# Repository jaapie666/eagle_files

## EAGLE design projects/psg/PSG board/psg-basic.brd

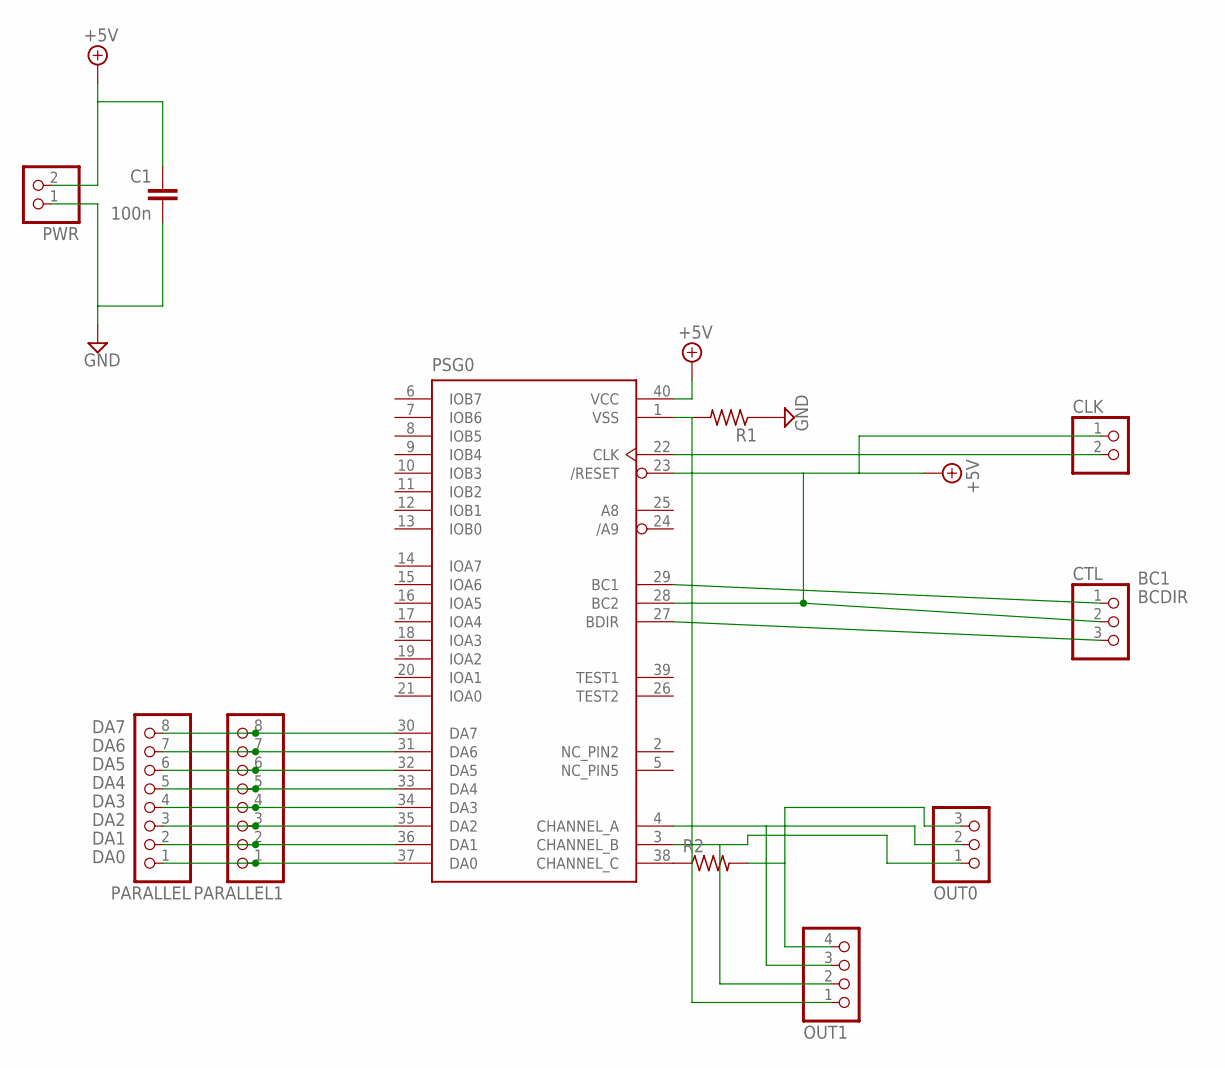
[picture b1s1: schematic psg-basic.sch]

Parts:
C1: 100n; 050X030_025
CLK: PINHD-1X2; 1X02
CTL: PINHD-1X3; 1X03
OUT0: PINHD-1X3; 1X03
OUT1: PINHD-1X4/90; 1X04/90
PARALLEL, PARALLEL1: PINHD-1X8; 1X08
PSG0: AY-3-8910; DIL40
PWR: PINHD-1X2; 1X02
R1: 6MM.4.1; R0207/4A
R2: 6MM.5; R0207/5

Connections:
+5V: C1.1, CLK.1, CTL.2, PSG0.23 (/RESET), PSG0.28 (BC2), PSG0.40 (VCC), PWR.2
BC1: CTL.1, PSG0.29 (BC1)
BCDIR: CTL.3, PSG0.27 (BDIR)
DA0: PARALLEL.1, PARALLEL1.1, PSG0.37 (DA0)
DA1: PARALLEL.2, PARALLEL1.2, PSG0.36 (DA1)
DA2: PARALLEL.3, PARALLEL1.3, PSG0.35 (DA2)
DA3: PARALLEL.4, PARALLEL1.4, PSG0.34 (DA3)
DA4: PARALLEL.5, PARALLEL1.5, PSG0.33 (DA4)
DA5: PARALLEL.6, PARALLEL1.6, PSG0.32 (DA5)
DA6: PARALLEL.7, PARALLEL1.7, PSG0.31 (DA6)
DA7: PARALLEL.8, PARALLEL1.8, PSG0.30 (DA7)
GND: C1.2, PWR.1, R1.1
unnamed: PSG0.38 (CHANNEL_C), R2.1
unnamed: OUT0.3, OUT1.4, R2.2
unnamed: CLK.2, PSG0.22 (CLK)
unnamed: OUT0.2, OUT1.3, PSG0.4 (CHANNEL_A)
unnamed: OUT0.1, OUT1.2, PSG0.3 (CHANNEL_B)
unnamed: OUT1.1, PSG0.1 (VSS), R1.2

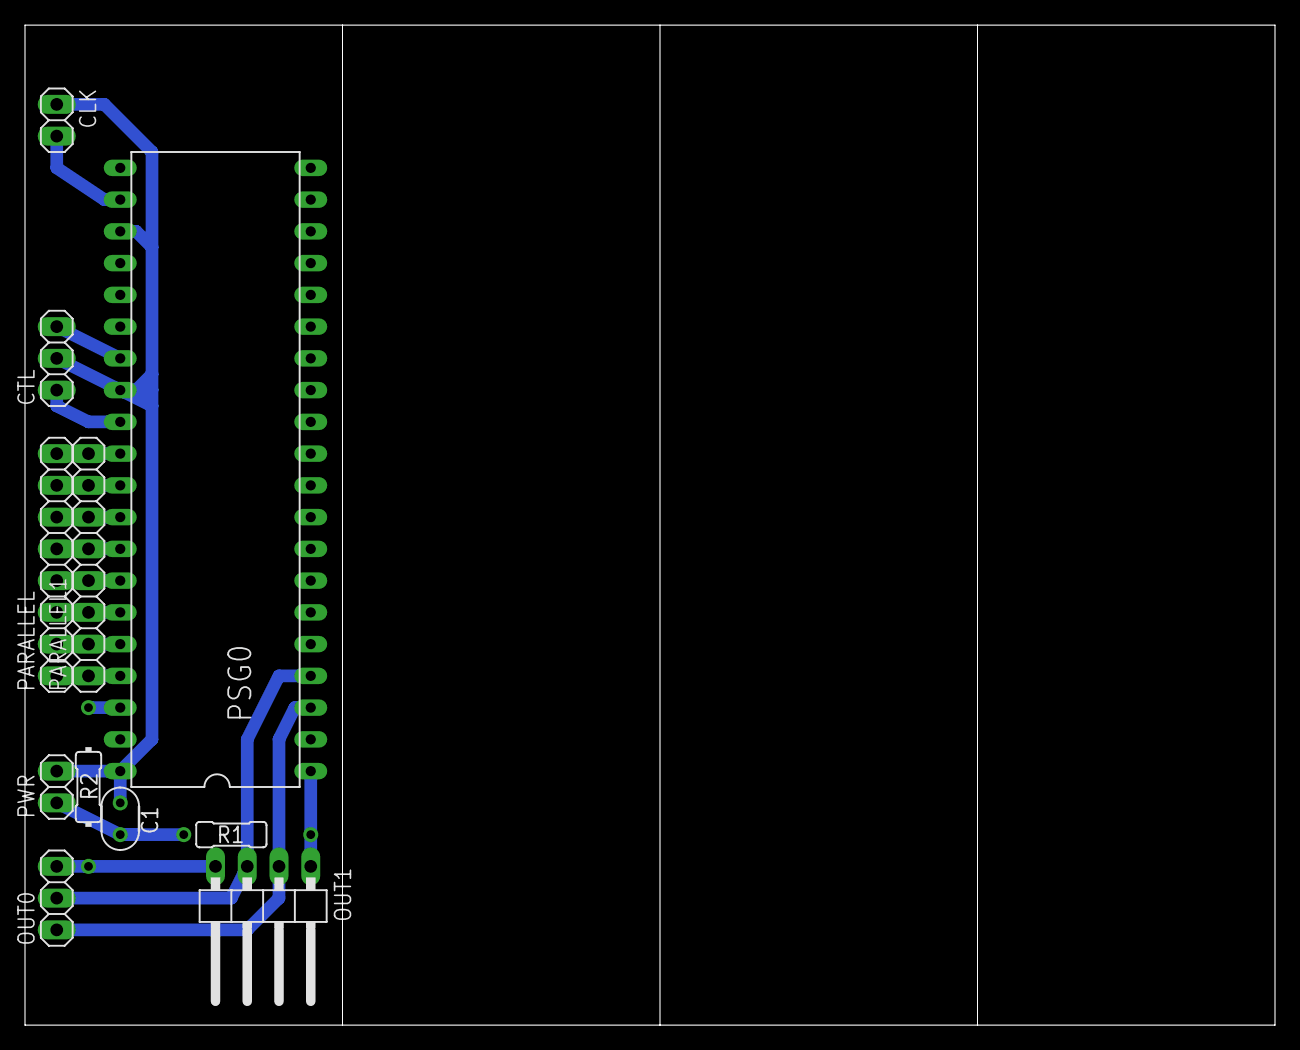
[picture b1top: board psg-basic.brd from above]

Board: 2 copper layers, 100.0 x 80.0 mm, 11 parts (0 on the bottom side), 18 nets.

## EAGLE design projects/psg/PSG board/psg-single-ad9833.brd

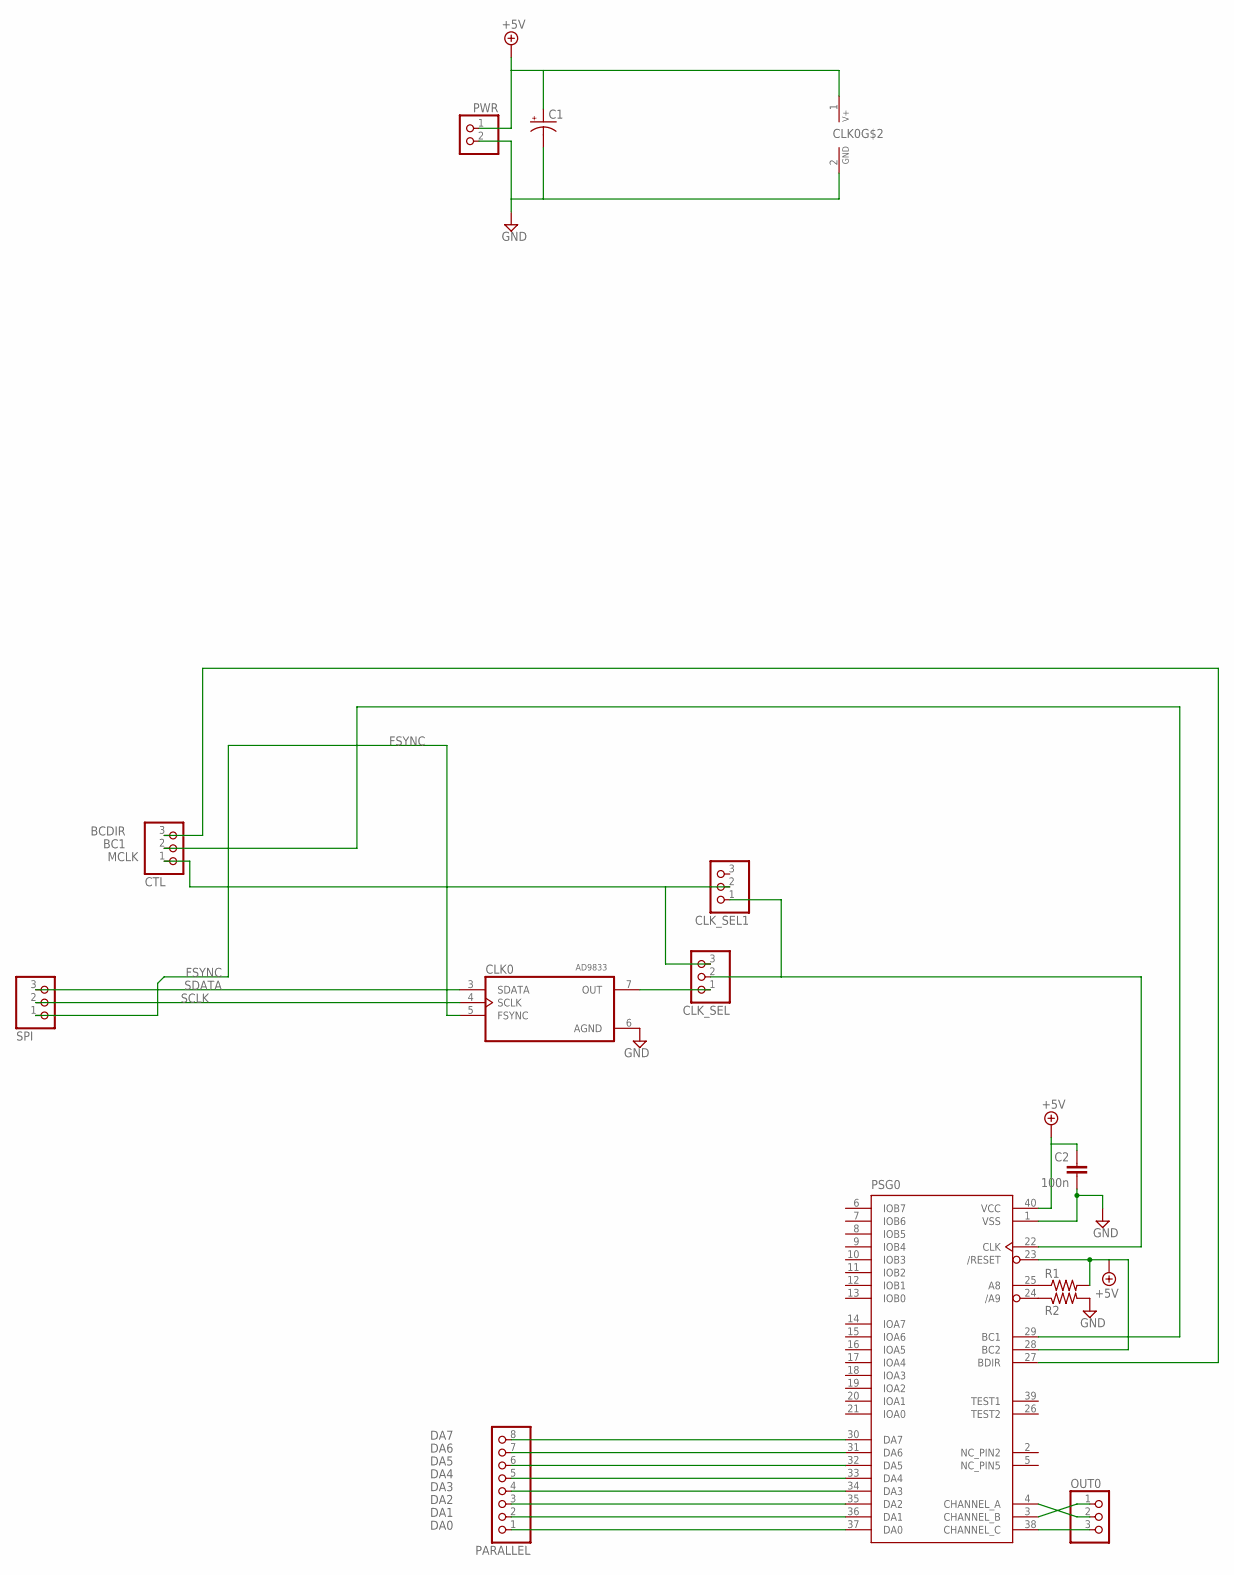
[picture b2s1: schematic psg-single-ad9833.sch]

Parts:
C1: 0501; 050_020_1
C2: 100n; 050X030_025
CLK0: AD9833_MODULE
CLK_SEL, CLK_SEL1: PINHD-1X3/90; 1X03/90
CTL: PINHD-1X3/90; 1X03/90
OUT0: PINHD-1X3/90; 1X03/90
PARALLEL: PINHD-1X8/90; 1X08/90
PSG0: AY-3-8910; DIL40
PWR: PINHD-1X2/90; 1X02/90
R1, R2: 6MM.3; R0207/3
SPI: PINHD-1X3/90; 1X03/90

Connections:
+5V: C1.+, C2.1, CLK0.1 (+V), PSG0.23 (/RESET), PSG0.28 (BC2), PSG0.40 (VCC), PWR.1, R1.2
BC1: CTL.2, PSG0.29 (BC1)
BCDIR: CTL.3, PSG0.27 (BDIR)
CLK_IN_0: CLK_SEL.2, CLK_SEL1.1, PSG0.22 (CLK)
DA0: PARALLEL.1, PSG0.37 (DA0)
DA1: PARALLEL.2, PSG0.36 (DA1)
DA2: PARALLEL.3, PSG0.35 (DA2)
DA3: PARALLEL.4, PSG0.34 (DA3)
DA4: PARALLEL.5, PSG0.33 (DA4)
DA5: PARALLEL.6, PSG0.32 (DA5)
DA6: PARALLEL.7, PSG0.31 (DA6)
DA7: PARALLEL.8, PSG0.30 (DA7)
FSYNC: CLK0.5 (FSYNC), SPI.1
GND: C1.-, C2.2, CLK0.2 (GND), CLK0.6 (AGND), PSG0.1 (VSS), PWR.2, R2.2
MCLK: CLK_SEL.3, CLK_SEL1.2, CTL.1
unnamed: CLK0.7 (OUT), CLK_SEL.1
unnamed: PSG0.24 (/A9), R2.1
unnamed: PSG0.25 (A8), R1.1
OUT_A: OUT0.2, PSG0.4 (CHANNEL_A)
OUT_B: OUT0.1, PSG0.3 (CHANNEL_B)
OUT_C: OUT0.3, PSG0.38 (CHANNEL_C)
SCLK: CLK0.4 (SCLK), SPI.2
SDATA: CLK0.3 (SDATA), SPI.3

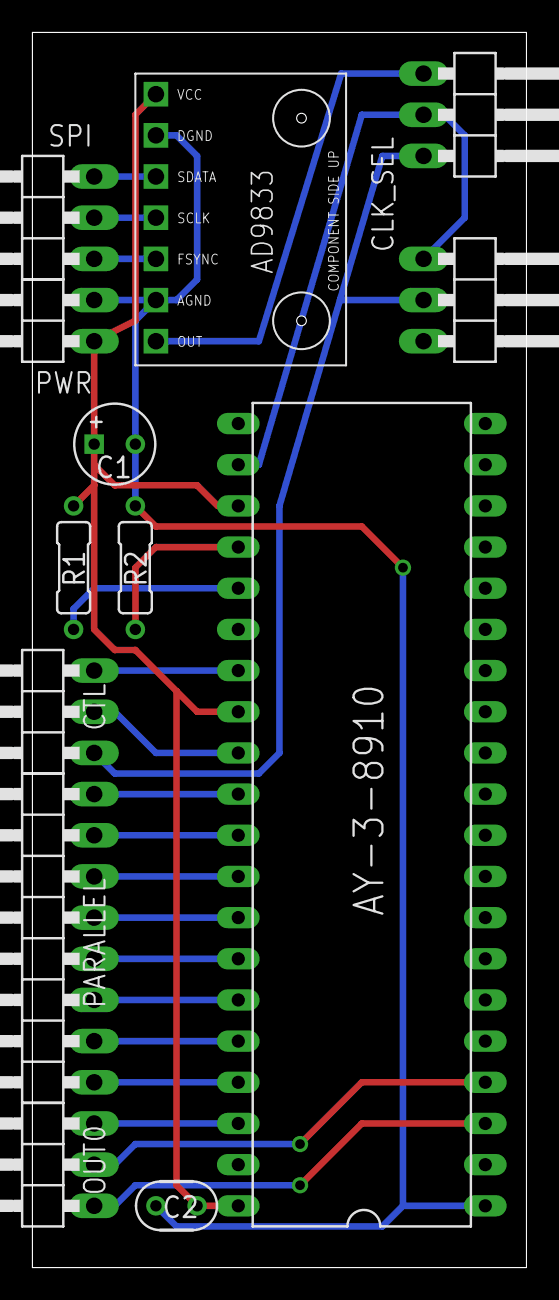
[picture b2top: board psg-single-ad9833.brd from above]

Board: 2 copper layers, 30.5 x 76.2 mm, 13 parts (0 on the bottom side), 23 nets.

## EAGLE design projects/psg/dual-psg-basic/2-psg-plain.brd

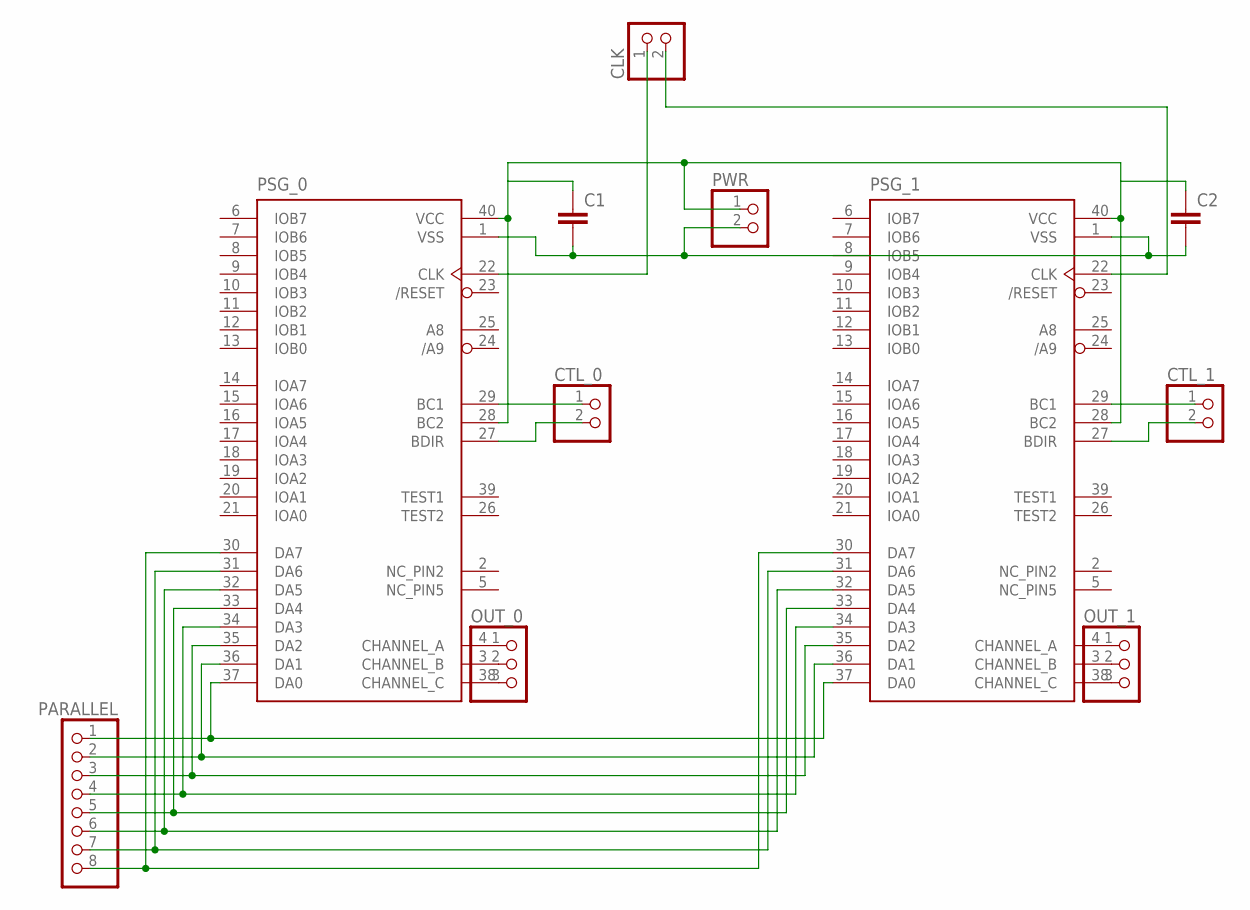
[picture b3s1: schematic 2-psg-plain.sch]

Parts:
C1, C2: 050X030_0251; 050X030_025
CLK: PINHD-1X2; 1X02
CTL_0, CTL_1: PINHD-1X2; 1X02
OUT_0, OUT_1: PINHD-1X3; 1X03
PARALLEL: PINHD-1X8; 1X08
PSG_0, PSG_1: AY-3-8910; DIL40
PWR: PINHD-1X2; 1X02

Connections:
GND: C1.2, C2.2, PSG_0.1 (VSS), PSG_1.1 (VSS), PWR.2
unnamed: CTL_0.2, PSG_0.27 (BDIR)
unnamed: CTL_0.1, PSG_0.29 (BC1)
unnamed: OUT_0.1, PSG_0.4 (CHANNEL_A)
unnamed: OUT_0.2, PSG_0.3 (CHANNEL_B)
unnamed: OUT_0.3, PSG_0.38 (CHANNEL_C)
unnamed: CTL_1.2, PSG_1.27 (BDIR)
unnamed: PARALLEL.1, PSG_0.37 (DA0), PSG_1.37 (DA0)
unnamed: OUT_1.1, PSG_1.4 (CHANNEL_A)
unnamed: PARALLEL.2, PSG_0.36 (DA1), PSG_1.36 (DA1)
unnamed: OUT_1.2, PSG_1.3 (CHANNEL_B)
unnamed: OUT_1.3, PSG_1.38 (CHANNEL_C)
unnamed: CLK.1, PSG_0.22 (CLK)
unnamed: CTL_1.1, PSG_1.29 (BC1)
unnamed: CLK.2, PSG_1.22 (CLK)
unnamed: PARALLEL.3, PSG_0.35 (DA2), PSG_1.35 (DA2)
unnamed: PARALLEL.4, PSG_0.34 (DA3), PSG_1.34 (DA3)
unnamed: PARALLEL.5, PSG_0.33 (DA4), PSG_1.33 (DA4)
unnamed: PARALLEL.6, PSG_0.32 (DA5), PSG_1.32 (DA5)
unnamed: PARALLEL.7, PSG_0.31 (DA6), PSG_1.31 (DA6)
unnamed: PARALLEL.8, PSG_0.30 (DA7), PSG_1.30 (DA7)
VCC: C1.1, C2.1, PSG_0.28 (BC2), PSG_0.40 (VCC), PSG_1.28 (BC2), PSG_1.40 (VCC), PWR.1

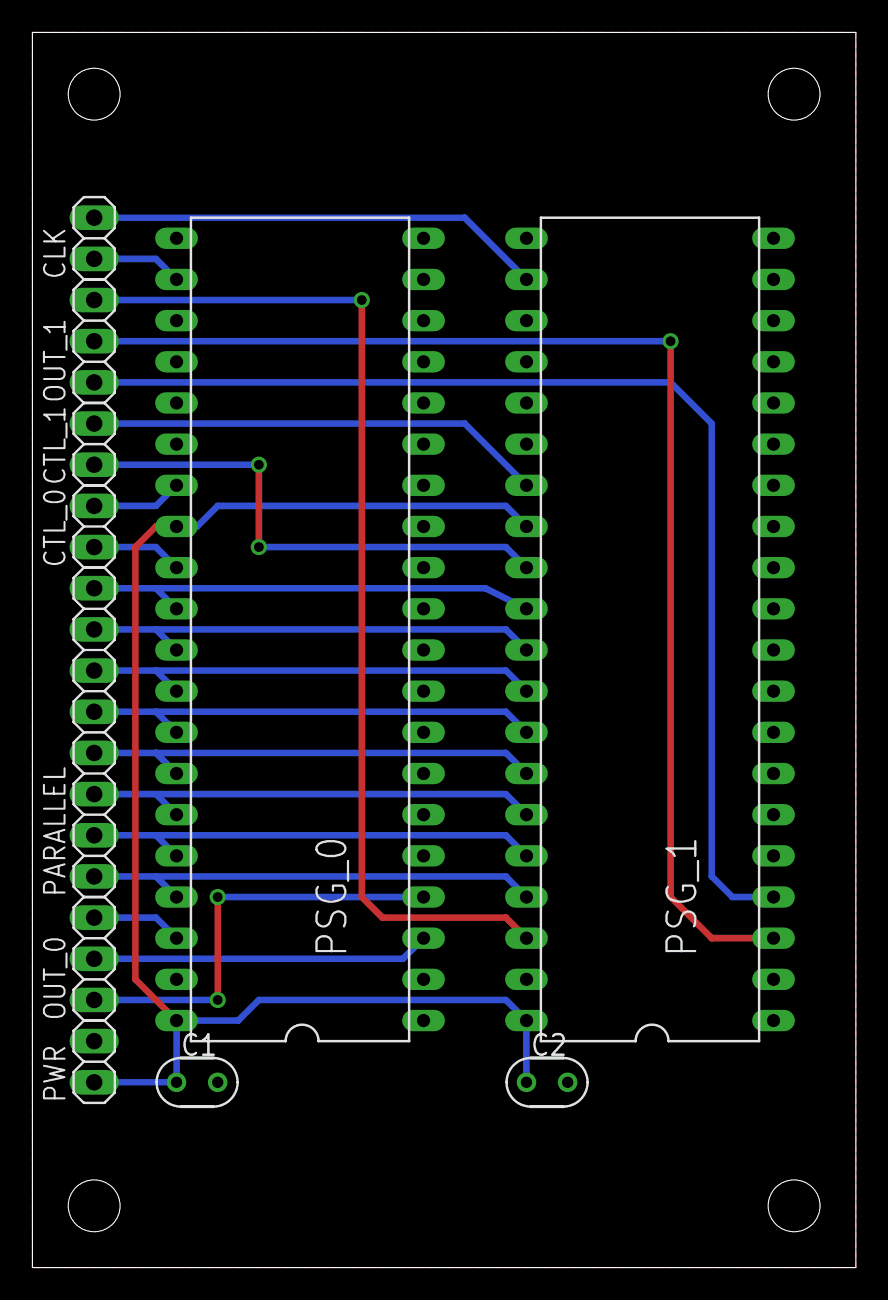
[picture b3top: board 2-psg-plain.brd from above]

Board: 2 copper layers, 50.8 x 76.2 mm, 11 parts (0 on the bottom side), 22 nets.

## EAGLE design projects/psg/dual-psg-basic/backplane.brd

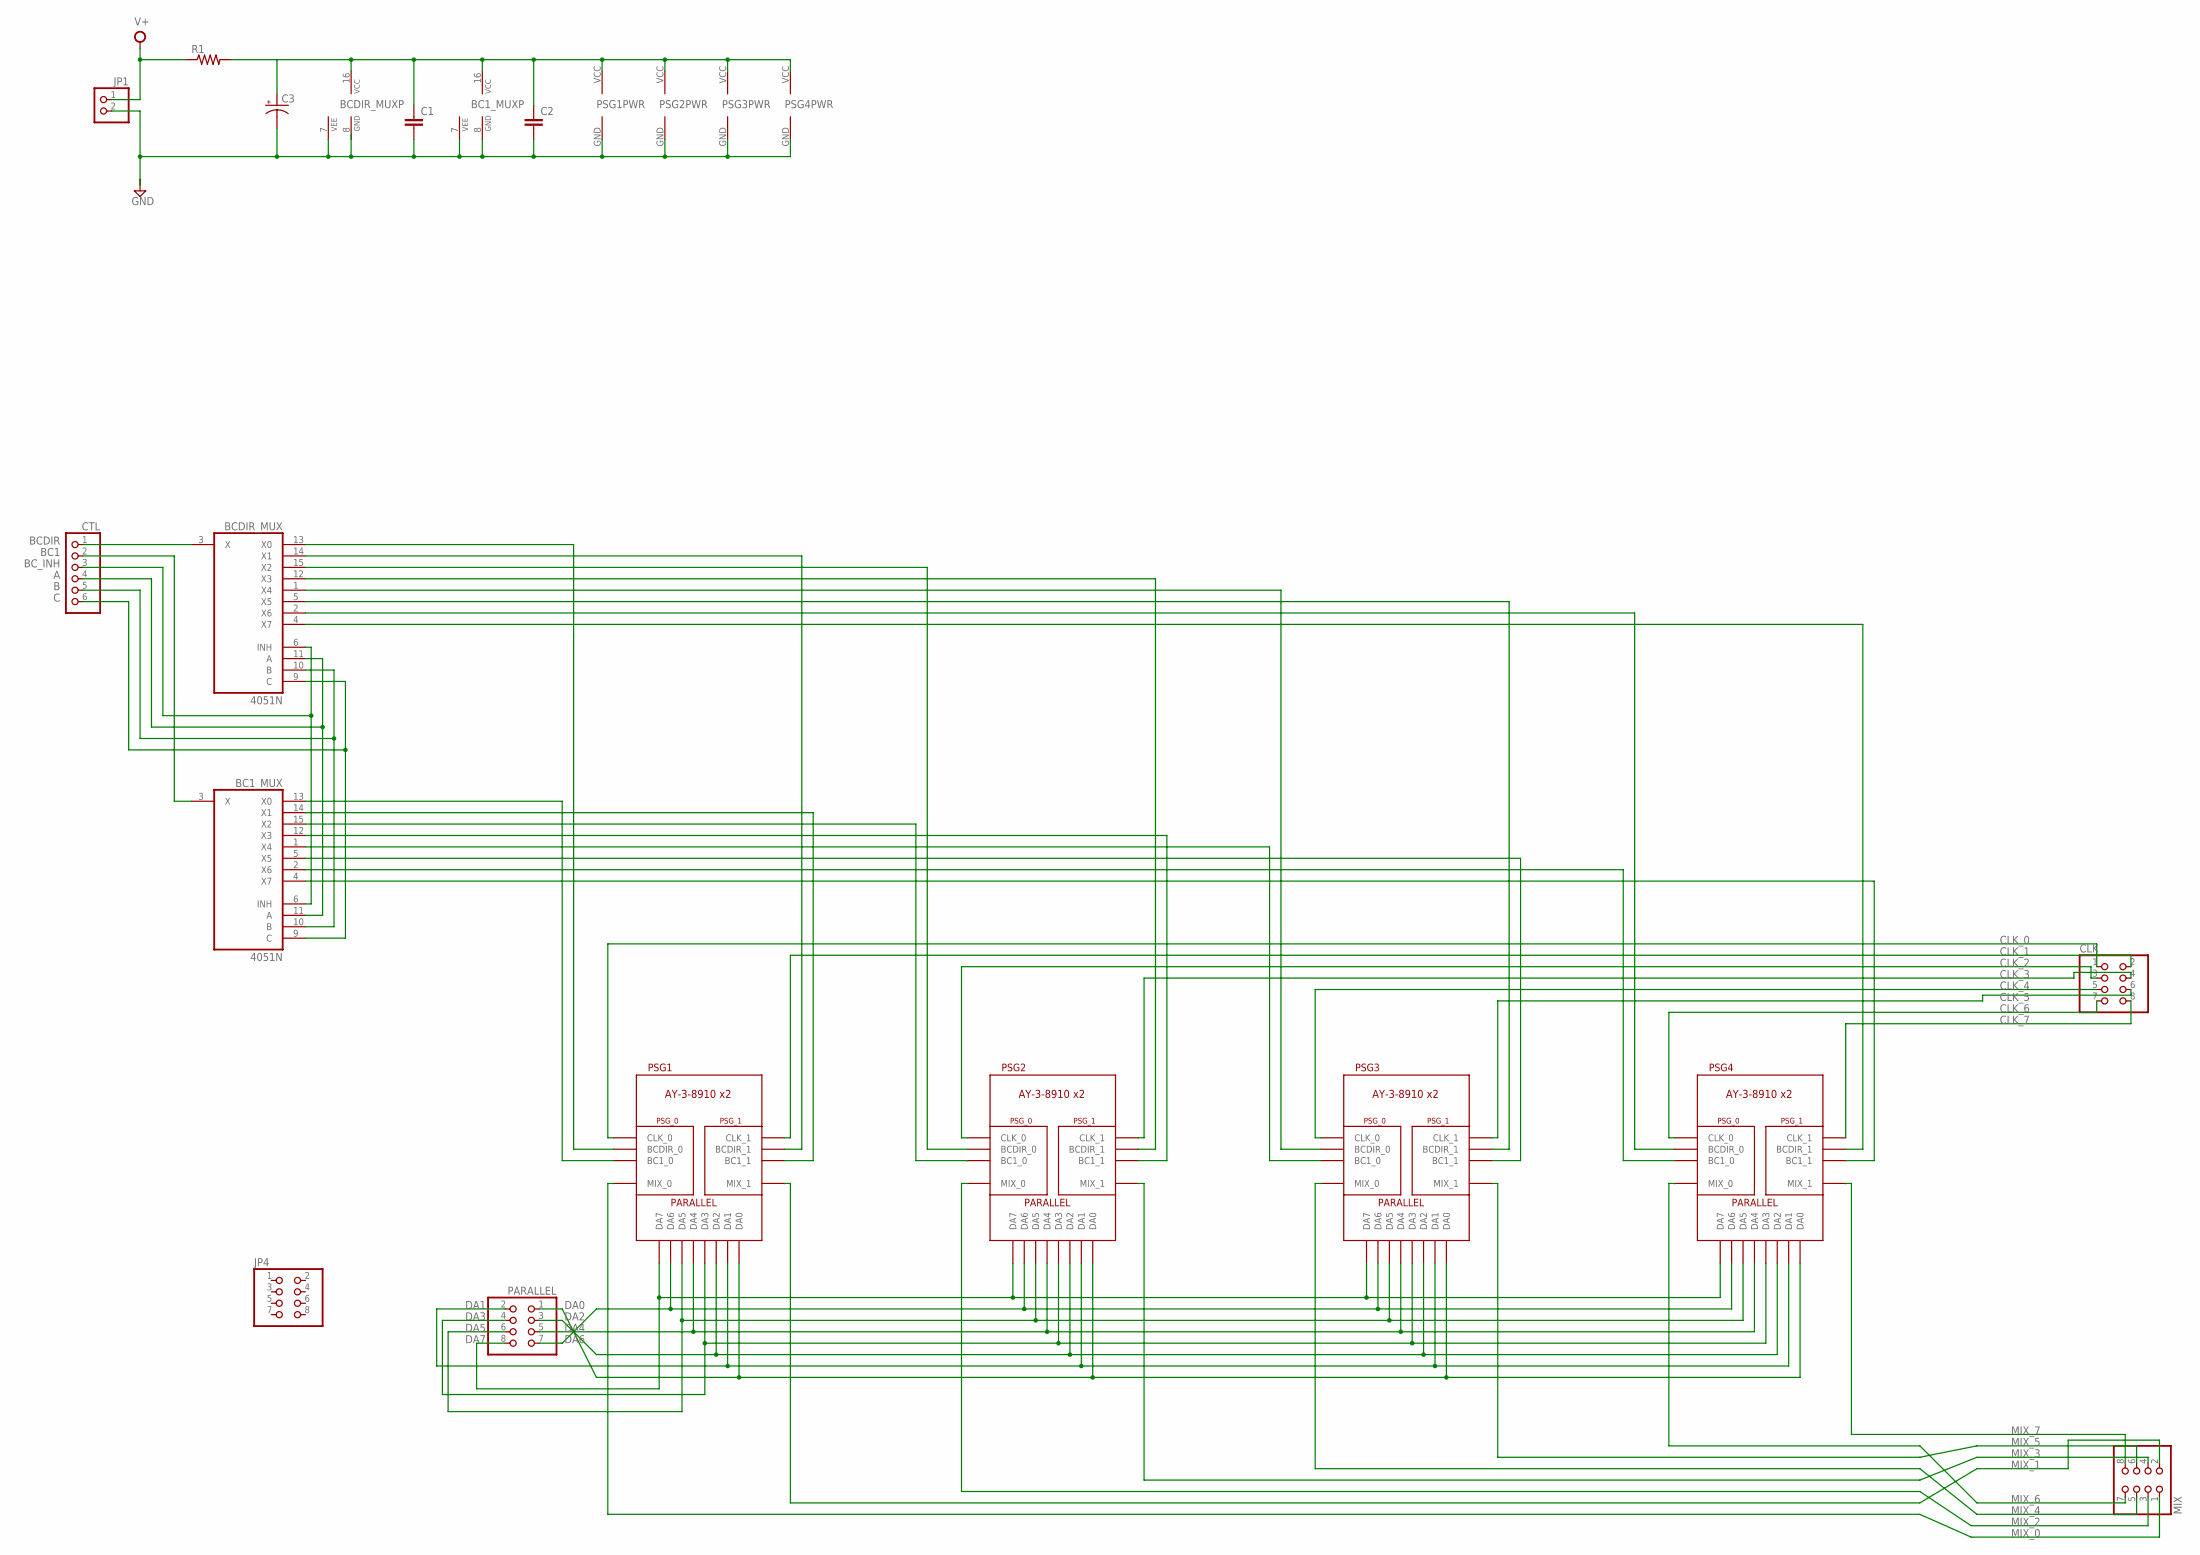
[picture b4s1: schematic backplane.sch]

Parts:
BC1_MUX: 4051N; DIL16
BCDIR_MUX: 4051N; DIL16
C1, C2: 050X030_0251; 050X030_025
C3: 0631; 063_025
CLK: PINHD-2X4; 2X04
CTL: PINHD-1X6; 1X06
JP1: PINHD-1X2; 1X02
JP4: PINHD-2X4; 2X04
MIX: PINHD-2X4; 2X04
PARALLEL: PINHD-2X4; 2X04
PSG1, PSG2, PSG3, PSG4: DUAL_PSG_DAUGHTER
R1: 6MM.3; R0207/3

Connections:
3: BCDIR_MUX.12 (X3), PSG2.BCDIR_1
A: BC1_MUX.11 (A), BCDIR_MUX.11 (A), CTL.4
B: BC1_MUX.10 (B), BCDIR_MUX.10 (B), CTL.5
BC1: BC1_MUX.3 (X), CTL.2
BC1_0: BC1_MUX.13 (X0), PSG1.BC1_0
BC1_1: BC1_MUX.14 (X1), PSG1.BC1_1
BC1_2: BC1_MUX.15 (X2), PSG2.BC1_0
BC1_3: BC1_MUX.12 (X3), PSG2.BC1_1
BC1_4: BC1_MUX.1 (X4), PSG3.BC1_0
BC1_5: BC1_MUX.5 (X5), PSG3.BC1_1
BC1_6: BC1_MUX.2 (X6), PSG4.BC1_0
BC1_7: BC1_MUX.4 (X7), PSG4.BC1_1
BCDIR: BCDIR_MUX.3 (X), CTL.1
BCDIR_0: BCDIR_MUX.13 (X0), PSG1.BCDIR_0
BCDIR_1: BCDIR_MUX.14 (X1), PSG1.BCDIR_1
BCDIR_2: BCDIR_MUX.15 (X2), PSG2.BCDIR_0
BCDIR_4: BCDIR_MUX.1 (X4), PSG3.BCDIR_0
BCDIR_5: BCDIR_MUX.5 (X5), PSG3.BCDIR_1
BCDIR_6: BCDIR_MUX.2 (X6), PSG4.BCDIR_0
BCDIR_7: BCDIR_MUX.4 (X7), PSG4.BCDIR_1
BC_INH: BC1_MUX.6 (INH), BCDIR_MUX.6 (INH), CTL.3
C: BC1_MUX.9 (C), BCDIR_MUX.9 (C), CTL.6
CLK_0: CLK.1, PSG1.CLK_0
CLK_1: CLK.2, PSG1.CLK_1
CLK_2: CLK.3, PSG2.CLK_0
CLK_3: CLK.4, PSG2.CLK_1
CLK_4: CLK.5, PSG3.CLK_0
CLK_5: CLK.6, PSG3.CLK_1
CLK_6: CLK.7, PSG4.CLK_0
CLK_7: CLK.8, PSG4.CLK_1
DA0: PARALLEL.1, PSG1.DA0, PSG2.DA0, PSG3.DA0, PSG4.DA0
DA1: PARALLEL.2, PSG1.DA1, PSG2.DA1, PSG3.DA1, PSG4.DA1
DA2: PARALLEL.3, PSG1.DA2, PSG2.DA2, PSG3.DA2, PSG4.DA2
DA3: PARALLEL.4, PSG1.DA3, PSG2.DA3, PSG3.DA3, PSG4.DA3
DA4: PARALLEL.5, PSG1.DA4, PSG2.DA4, PSG3.DA4, PSG4.DA4
DA5: PARALLEL.6, PSG1.DA5, PSG2.DA5, PSG3.DA5, PSG4.DA5
DA6: PARALLEL.7, PSG1.DA6, PSG2.DA6, PSG3.DA6, PSG4.DA6
DA7: PARALLEL.8, PSG1.DA7, PSG2.DA7, PSG3.DA7, PSG4.DA7
GND: BC1_MUX.7 (VEE), BC1_MUX.8 (GND), BCDIR_MUX.7 (VEE), BCDIR_MUX.8 (GND), C1.2, C2.2, C3.-, JP1.2, PSG1.GND, PSG2.GND, PSG3.GND, PSG4.GND
MIX_0: MIX.1, PSG1.MIX_0
MIX_1: MIX.2, PSG1.MIX_1
MIX_2: MIX.3, PSG2.MIX_0
MIX_3: MIX.4, PSG2.MIX_1
MIX_4: MIX.5, PSG3.MIX_0
MIX_5: MIX.6, PSG3.MIX_1
MIX_6: MIX.7, PSG4.MIX_0
MIX_7: MIX.8, PSG4.MIX_1
unnamed: BC1_MUX.16 (VCC), BCDIR_MUX.16 (VCC), C1.1, C2.1, C3.+, PSG1.VCC, PSG2.VCC, PSG3.VCC, PSG4.VCC, R1.2
V+: JP1.1, R1.1

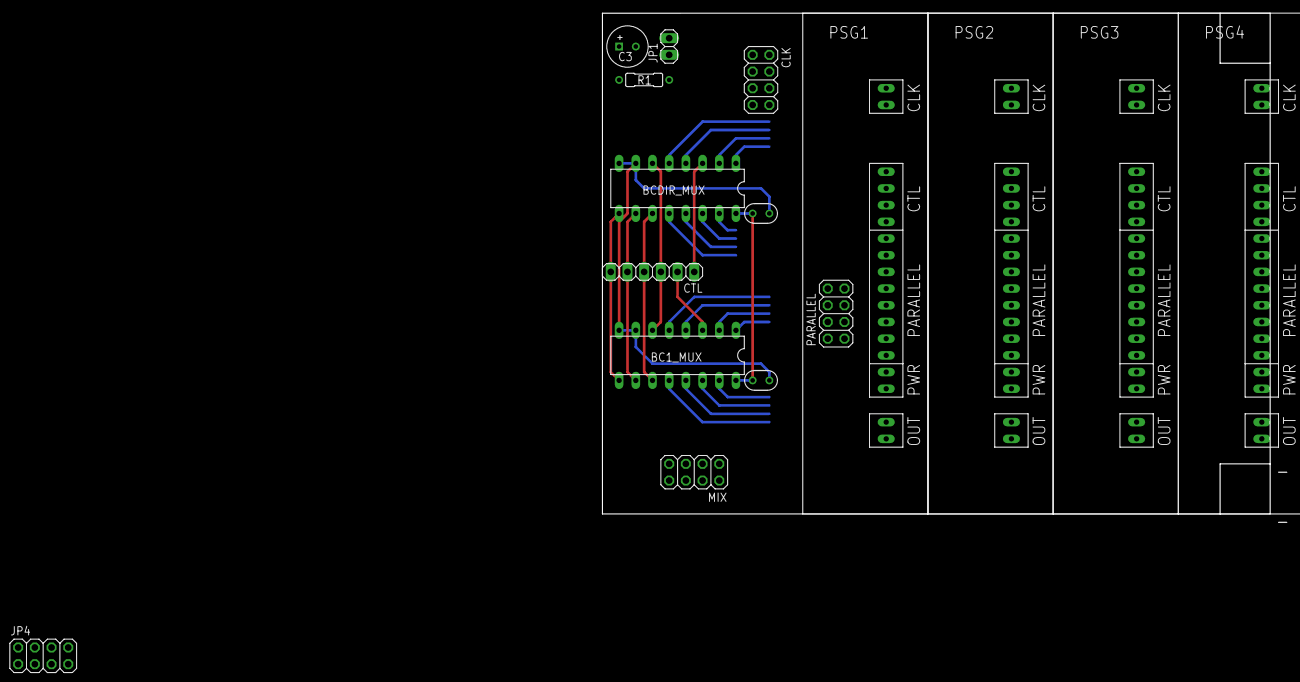
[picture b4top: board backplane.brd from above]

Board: 2 copper layers, 104.1 x 77.5 mm, 16 parts (0 on the bottom side), 49 nets.
